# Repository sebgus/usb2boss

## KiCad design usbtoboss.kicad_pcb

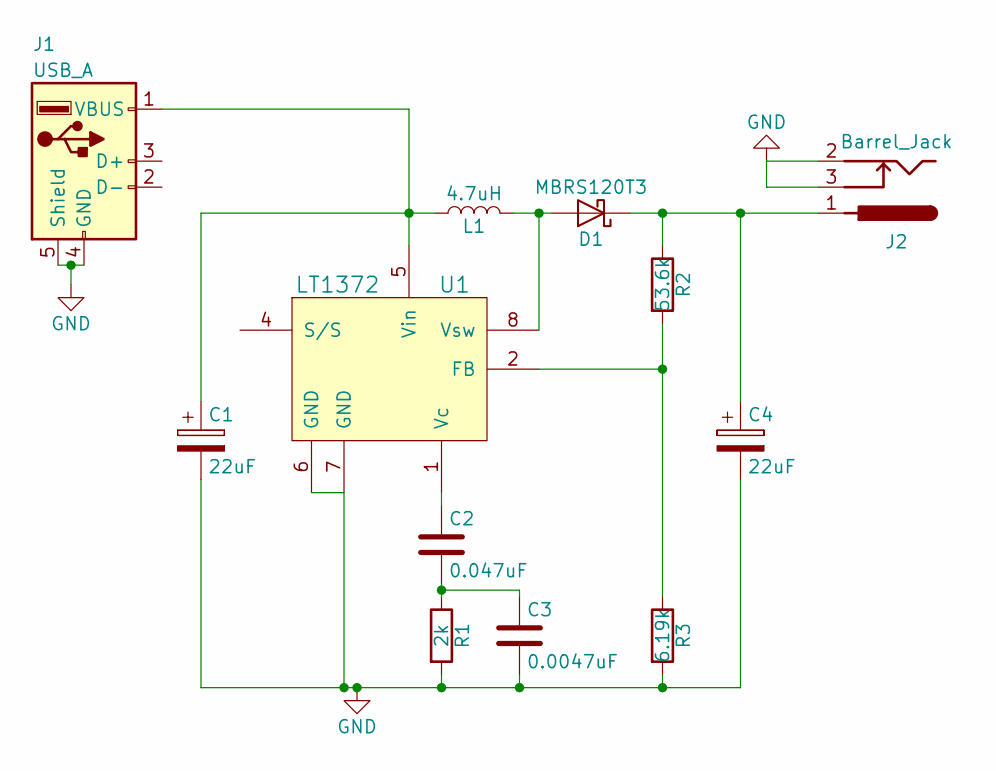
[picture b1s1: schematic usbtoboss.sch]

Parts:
C1, C4: 22uF; CP_Elec_8x10
C2: 0.047uF; C_0603
C3: 0.0047uF; C_0603
D1: MBRS120T3; D_0805
J1: USB_A; USB3_A_Molex_48393-001
J2: Barrel_Jack; Barrel_Jack_CUI_PJ-036AH-SMT
L1: 4.7uH; L_0805
R1: 2k; R_0603
R2: 53.6k; R_0603
R3: 6.19k; R_0603
U1: LT1372; SO-8_5.3x6.2mm_Pitch1.27mm

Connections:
GND: C1.2, C3.2, C4.2, J1.4 (GND), J1.5 (Shield), J2.2, J2.3, R1.2, R3.2, U1.6 (GND), U1.7 (GND)
unnamed: C1.1, J1.1 (VBUS), L1.1, U1.5 (Vin)
unnamed: C2.1, U1.1 (Vc)
unnamed: C2.2, C3.1, R1.1
unnamed: C4.1, D1.1 (K), J2.1, R2.1
unnamed: D1.2 (A), L1.2, U1.8 (Vsw)
unnamed: R2.2, R3.1, U1.2 (FB)

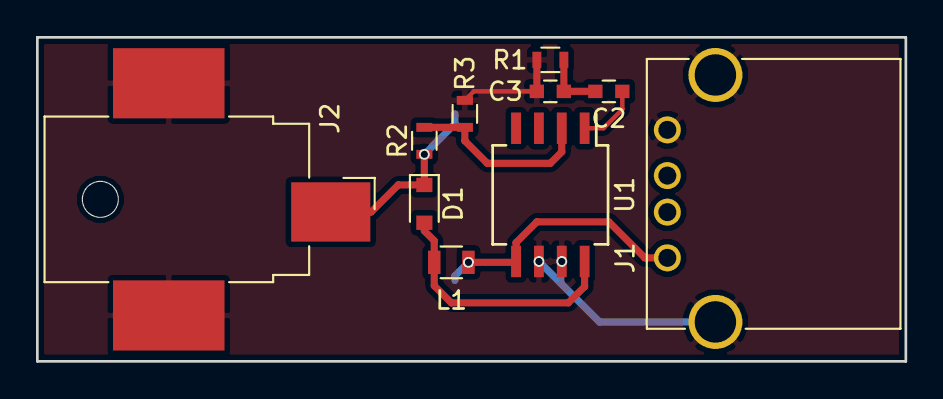
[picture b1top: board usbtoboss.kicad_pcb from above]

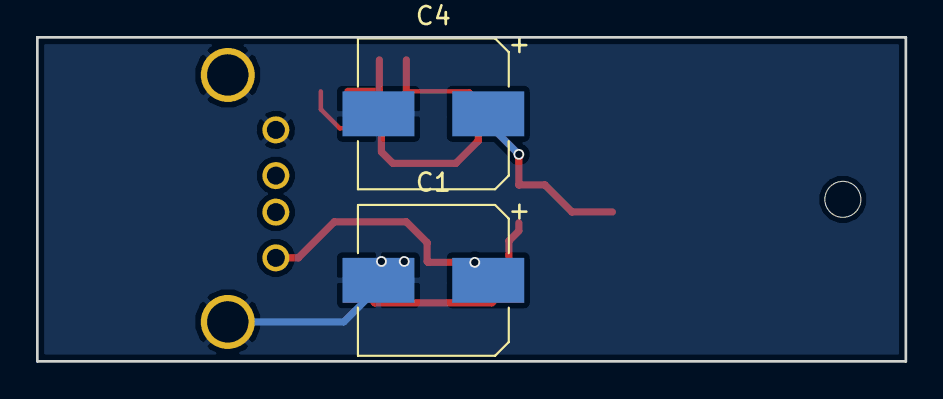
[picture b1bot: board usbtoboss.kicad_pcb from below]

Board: 2 copper layers, 48.2 x 18.0 mm, 12 parts (2 on the bottom side), 7 nets.

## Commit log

2017-12-19 Initial design
    Rough schematic and pcb layout design.
